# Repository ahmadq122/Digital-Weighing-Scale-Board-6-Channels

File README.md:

# Digital-Weighing-Scale-Board-6-Channels
The board uses ESP32 Dev Board as the microcontroller with Nextion 3.2" LCD Touch as a User Interface, made in portable form, and easy to use. Real Time Operating System (FreeRTOS) was applied to get better code structure and device performance. Weighing can be performed on 6 different objects at the same time, with adjustable maximum weighing on each channel. Use 3 pcs of IC ADS1232 as an Analog to Digital Converter. Calibration sensor feature available, with a maximum of 8 calibration points. 3 data logging models are available, which are Local via Micro SD card, Serial RS232, and logging through ThingSpeak.

Code programming is done in IDE: Platform IO - Visual Studio Code Framework: Arduino

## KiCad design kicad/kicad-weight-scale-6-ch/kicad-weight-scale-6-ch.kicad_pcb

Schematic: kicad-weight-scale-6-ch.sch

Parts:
BT1: 18650 Li-ion; TerminalBlock_bornier-2_P5.08mm
BZ1: Buzzer; Buzzer_12x9.5RM7.6
C1: 220u; CP_Radial_D7.5mm_P2.50mm
C2: 100U; CP_Radial_D7.5mm_P2.50mm
D1, D2, D3: D_Schottky; D_SMA-SMB_Universal_Handsoldering
J1: Barrel_Jack_Switch; BarrelJack_Horizontal
J2, J6, J7, J8, J9: Conn_01x02; PinHeader_1x02_P2.54mm_Vertical
J3, J4, J5: Conn_01x04; PinHeader_1x04_P2.54mm_Vertical
Q1, Q2: Si4542DY; SOIC-8_3.9x4.9mm_P1.27mm
Q3: BSS138; SOT-23
R1, R2, R3: 10k; R_0805_2012Metric_Pad1.20x1.40mm_HandSolder
R4: 27k; R_0805_2012Metric_Pad1.20x1.40mm_HandSolder
R5, R6, R7, R10, R11: 1M; R_0805_2012Metric_Pad1.20x1.40mm_HandSolder
R8: 100k; R_0805_2012Metric_Pad1.20x1.40mm_HandSolder
R9: 1k; R_0805_2012Metric_Pad1.20x1.40mm_HandSolder
SW1: SW_Push; PinHeader_1x02_P2.54mm_Vertical
U1: TP-4056; Li-ion ic charger
U2: StepUpTo5V; Step up 5V
U3, U5, U7: WCMCU-ADS1232; wcmcu-ads1232
U4: ESPWROOM32; esp wroom 32 board
U6: DataLoggingBoard; Datalogging board
U8, U9, U10, U11, U12, U13: USB_Type_C; Type C Converter

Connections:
3V3: U3.10 (DVDD/1), U4.1, U5.10 (DVDD/1), U7.10 (DVDD/1)
5V: D2.2 (A), J9.1, Q2.4 (G), R5.2
A0_1: U3.13 (A0/8), U4.13
A0_2: U4.10, U5.13 (A0/8)
A0_3: U4.24, U7.13 (A0/8)
AINN1_1: U3.15 (AINN1/12), U8.4, U8.10
AINN1_2: U5.15 (AINN1/12), U10.4, U10.10
AINN1_3: U7.15 (AINN1/12), U12.4, U12.10
AINN2_1: U3.17 (AINN2/13), U9.4, U9.10
AINN2_2: U5.17 (AINN2/13), U11.4, U11.10
AINN2_3: U7.17 (AINN2/13), U13.4, U13.10
AINP1_1: U3.16 (AINP1/11), U8.3, U8.9
AINP1_2: U5.16 (AINP1/11), U10.3, U10.9
AINP1_3: U7.16 (AINP1/11), U12.3, U12.9
AINP2_1: U3.18 (AINP2/14), U9.3, U9.9
AINP2_2: U5.18 (AINP2/14), U11.3, U11.9
AINP2_3: U7.18 (AINP2/14), U13.3, U13.9
BUZZ: Q3.1, R11.2, U4.29
CLKIN_1: J6.1, U3.14 (CLKIN/3)
CLKIN_2: J7.1, U5.14 (CLKIN/3)
CLKIN_3: J8.1, U7.14 (CLKIN/3)
DATA_1: U3.5 (24/~DRDY~/DOUT), U4.12
DATA_2: U4.9, U5.5 (24/~DRDY~/DOUT)
DATA_3: U4.23, U7.5 (24/~DRDY~/DOUT)
EN: J2.1, U4.2
GND: BT1.2 (-), C1.2, C2.2, J1.2, J1.3, J2.2, J3.4, J4.4, J5.4, J6.2, J7.2, J8.2, Q1.1 (S), Q3.2, R5.1, R6.1, R7.2, R8.2, R10.2, R11.1, U1.3 (B-), U1.4 (OUT-), U1.5 (GND), U2.2, U2.4, U3.8 (17/AGND), U3.11 (DGND/2), U3.12 (TEMP/7), U4.14, U4.32, U4.38, U5.8 (17/AGND), U5.11 (DGND/2), U5.12 (TEMP/7), U6.2 (GND), U6.8 (CS), U7.8 (17/AGND), U7.11 (DGND/2), U7.12 (TEMP/7), U8.6, U8.7, U9.6, U9.7, U10.6, U10.7, U11.6, U11.7, U12.6, U12.7, U13.6, U13.7
MISO: U4.31, U6.6 (MISO)
MOSI: U4.37, U6.7 (MOSI)
unnamed: BZ1.2 (+), Q3.3
unnamed: D1.2 (A), Q2.5 (D), Q2.6 (D), R6.2
unnamed: D3.2 (A), R9.2, SW1.2
unnamed: J1.1, J9.2, U1.6 (5V)
unnamed: Q1.4 (G), Q1.7 (D), Q1.8 (D), R2.2
RXD0: J3.2, U4.34
RXD1: J4.2, U4.16
RXD2: J5.2, U4.27
SCK: U4.30, U6.5 (SCK)
SCL: U4.36, U6.4 (SCL)
SCLK_1: U3.6 (23/SCLK), U4.11
SCLK_2: U4.8, U5.6 (23/SCLK)
SCLK_3: U4.15, U7.6 (23/SCLK)
SDA: U4.33, U6.3 (SDA)
SPEED: U3.3 (21/SPEED), U4.26, U5.3 (21/SPEED), U7.3 (21/SPEED)
TXD0: J3.3, U4.35
TXD1: J4.3, U4.17
TXD2: J5.3, U4.28
VCC: BZ1.1 (-), C2.1, J3.1, J4.1, J5.1, R1.1, R3.1, U2.3, U3.1 (19/GAIN0), U3.2 (20/GAIN1), U3.7 (16/REFP), U3.9 (18/AVDD), U4.19, U5.1 (19/GAIN0), U5.2 (20/GAIN1), U5.7 (16/REFP), U5.9 (18/AVDD), U6.1 (5V), U7.1 (19/GAIN0), U7.2 (20/GAIN1), U7.7 (16/REFP), U7.9 (18/AVDD), U8.1, U8.12, U9.1, U9.12, U10.1, U10.12, U11.1, U11.12, U12.1, U12.12, U13.1, U13.12
VCC_1: C1.1, D1.1 (K), D2.1 (K), Q1.3 (1), R2.1, SW1.1
VCC_2: D3.1 (K), Q1.5 (D), Q1.6 (D), U2.1
VCC_B: BT1.1 (+), R4.1, U1.2 (B+)
VCC_B1: Q2.3 (1), U1.1 (OUT+)
VCC_B_SENSE: R4.2, R8.1, U4.6
VCC_CNTRL: Q1.2 (G), R7.1, U4.25
VCC_SENSE: R9.1, R10.1, U4.5
~CHRG: R1.2, U1.8 (~CHRG), U4.3
~PWDN: U3.4 (22/~PWDN~), U4.7, U5.4 (22/~PWDN~), U7.4 (22/~PWDN~)
~STDBY: R3.2, U1.7 (~STDBY), U4.4

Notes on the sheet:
add diode, and move vcc sens junction

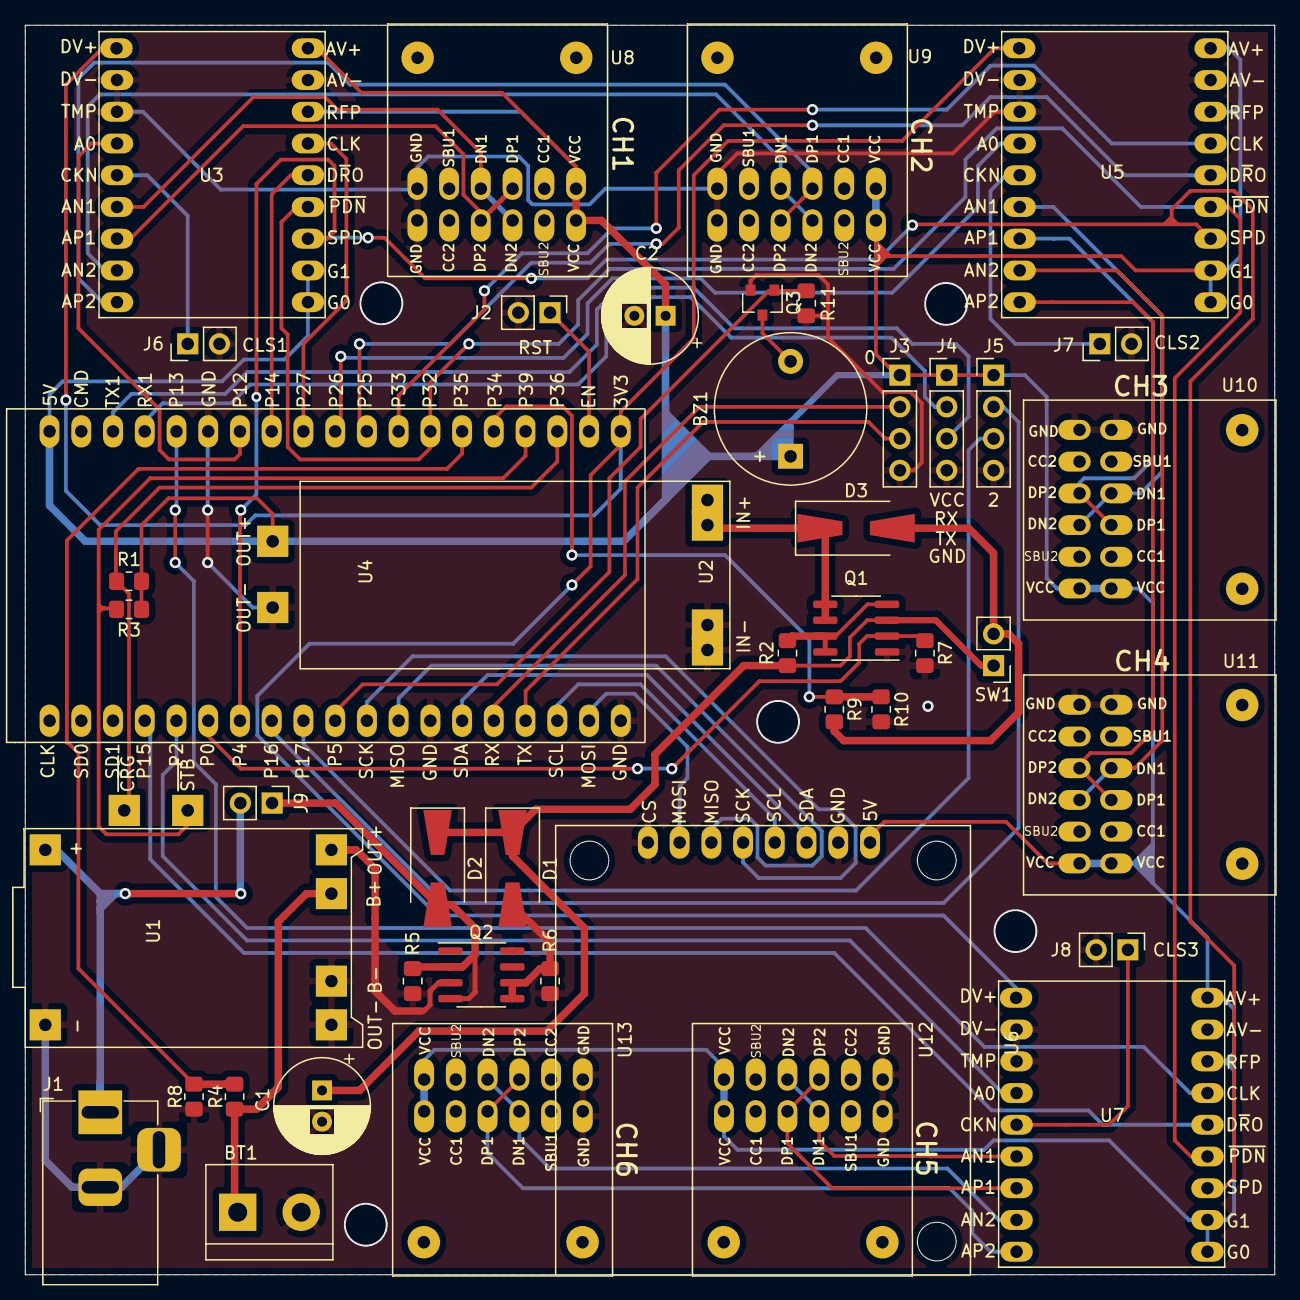
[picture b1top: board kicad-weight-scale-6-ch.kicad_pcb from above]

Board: 2 copper layers, 100.0 x 100.0 mm, 44 parts (0 on the bottom side), 57 nets.

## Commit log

2021-03-27 init
2021-03-28 Remove Interrupt Timer, applied FreeRTOS instead
2021-03-28 Add Task_02 to run hmi.serialEvent_2()
2021-03-28 Auto dim screen, store brightness, store index baudrate, fix bug open page, fix stack overflow Task_01
2021-03-28 set the screen brightness at strtup, detect the touch on all part of the page and wake up the brightness
2021-03-28 fix bug: can't set the brightness at start up
2021-03-28 Send auto dim once to nextion after auto dim timer achieved
2021-03-29 printDebug, put ads1232 data reading into Task_04, Task_05, and Task_06 to be run independently
2021-04-02 Update StartProgressBar, Single PWDN pin, Disable auto create data logger at setup(), Backend Zero Sensor
2021-04-03 Fix POint Calibrationt Page
2021-04-04 Complete Datalog Page, Re-arrang the data structure, apply page timeout, re-init baudrate serial if any changes,
2021-04-06 Add data logs schedule checker
2021-04-06 ThingSpeak Logger
2021-04-11 Update Kicad, PinMap, Utility
2021-04-18 update PCB deisgn
2021-05-17 Update nextion-esp32dws6chwl_ench.HMI, kicad-weight-scale-6-ch-cache.lib, and 6 more files...
2021-05-18 Update nextion-esp32dws6chwl_ench.HMI, PictureListID.h, and 2 more files...
2021-05-20 Update nextion-esp32dws6chwl_ench.HMI, Settings.cpp, and 4 more files...
2021-05-20 Update nextion-esp32dws6chwl_ench.HMI, Datalogger.cpp, and 6 more files...
2021-05-23 Update nextion-esp32dws6chwl_ench.HMI, Datalogger.cpp, and 7 more files...
2021-05-30 Update settings.json, nextion-esp32dws6chwl_ench.HMI, and 15 more files...
2021-06-02 Update settings.json, nextion-esp32dws6chwl_ench.HMI, and 10 more files...
2021-06-05 Update ADS1232.cpp, Datalogger.cpp, and 3 more files...
2021-06-07 Update nextion-esp32dws6chwl_ench.HMI, ADS1232.cpp, and 7 more files...
2021-06-19 Update nextion-esp32dws6chwl_ench.HMI, kicad-weight-scale-6-ch.kicad_pcb, and 20 more files...
2021-07-12 Update .gitignore, README.md, and 15 more files...
2021-09-14 Update settings.json, RTOS.cpp, and 2 more files...
